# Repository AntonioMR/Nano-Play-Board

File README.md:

# Nano-Play-Board
Esta placa pretende ser una herramienta de iniciación a la experimentación y aprendizaje de recursos de programación y electrónica con la placa [Arduino Nano 3.x][3] o compatibles.
Dispone de varios sensores, actuadores y puertos para la conexión con otras placas de forma que sea posible explotar parte de las funcionalidades de la plataforma Arduino.

[José Juan Sánchez][1] ha desarrollado una librería para usar la placa que que se encuentra disponile en su [cuenta de github][2]. Esta librería permite un uso fácil de los recursos disponibles en la placa mediante el uso de las clases definidas para los distionts elementos y los metodos para la interactuación con los mismos. 

## Sensores
- Una fotoresistencia conectada al pin de entrada analógica A6.
- Un potenciómetro conectado al pin de entrada analógica A7.
- Cuatro pulsadores conectados a los pines PB0-3 del expansor de GPIO.
- Un acelerómetro de tres ejes conectado a los pines A4 y A5 por medio del bus I2C.
- Un encoder incremental de 16 pasos/revolución conectado a los pines D2 y D5.

## Actuadores
- Un buzzer conectado al canal 7 del driver para LED's.
- Un led RGB conectado a los canales 4, 5 y 6 (rojo, azul y verde respectivamente).
- Una matriz de led's conectada a los pines PA0-7 y PB4-7 del expansor de GPIO, para indicar la columna a encender como el patrón a visualizar en la columna. 

## Puertos
- Un zócalo hembra para conectar un detector de objetos por ultrasonidos conectado a los pines D7 y D8.
- Dos zócalos para conectar foto-receptores de infrarrojos tipo CNY-70 conectados a los pines D6 y D9.
- Un zócalo hembra para conectar un sensor de temperatura y humedad tipo DTH11/DTH22 conectado al pin D12.
- Cuatro zócalos macho para conectar servomotores controlados mediante los canales 0-4 del driver para LED's conectado por I2C.
- Un zócalo hembra para conectar un modulo Bluetooth HC-05/HC-6 mediante los pines D10 y D11.
- Un zócalo hembra para conectar un modulo Wifi ESP8266 mediante los pines D10 y D11.
- Cuatro pads para la conexion de sensores capacitivos a los pines A0, A1, A2 y A3.

## Estructura del repositorio
- Raiz: Fuentes del proyecto de la placa de circuito impreso para el software de diseño de PCB [KiCad][4].
- Gerber : Ficheros de fabricacion en formato Gerber de la placa de circuito impreso.
- Imagenes : Renders de la placa de circuito impreso.
- Pdf : Ficheros para el montaje en formato pdf. Esquema del circuito, situacion de componentes, etc.
- Modelos3D : Modelos 3D en formato .wrl para la visualizacion en el proyecto del diseño de la PCB.
- Soft/lib : Librerías para el uso de los distintos elementos presentes en la placa.
- Soft/src : Ejemplos de uso de la placa. 

## Imagenes
Cara superior

Cara inferior

## Lista de materiales
Refencias | Valor | Total Uds
----------|-------|-----------
| R1, R2, R20, R21, R22, R3, R4, R5, R6, R7 | [Resistencia 120 Ohm 1/8W](http://www.tme.eu/es/details/crcw0805120rfktabc/resistencias-smd-0805/vishay/) | 10
| R8, R9, R10, R11, R12, R13, R38, R40, R42, R49, R52,  | [Resistencia 1 KOhm 1/8W](http://www.tme.eu/es/details/crcw08051k00fkea/resistencias-smd-0805/vishay/) | 11
| R14 | [Resistencia 2 KOhm 1/8W](http://www.tme.eu/es/details/crcw08052k00fktabc/resistencias-smd-0805/vishay/) | 1
| R23, R32, R33, R34, R35  | [Resistencia 4.7 KOhm 1/8W](http://www.tme.eu/es/details/crcw08054k70fkea/resistencias-smd-0805/vishay/) | 5
| R15, R16, R17, R18, R19, R24, R25, R26, R27, R36, R39, R41, R47, R50 | [Resistencia 10 KOhm 1/8W](http://www.tme.eu/es/details/crcw080510k0fkea/resistencias-smd-0805/vishay/) | 14
| R43, R45  | [Resistencia 220 Ohm 1/8W](http://www.tme.eu/es/details/rc0805fr-07220r/resistencias-smd-0805/yageo/rc0805fr-07220rl/) | 2
| R44, R46, R48, R51  | [Resistencia 47 KOhm 1/8W](http://www.tme.eu/es/details/rc0805fr-0747k/resistencias-smd-0805/yageo/rc0805fr-0747kl/) | 4
| R28, R29, R30, R31 | [Resistencia 10 MOhm 1/8W](http://www.tme.eu/es/details/crcw080510k0fkea/resistencias-smd-0805/vishay/) | 4
| R37 | [Resistencia LDR](http://www.tme.eu/es/details/gm7516/fotoresistencias/wodeyijia/) | 1
| RV1 | [Potenciometro 10K](https://es.rs-online.com/web/p/potenciometros/7293622/)| 1
| C1, C2 | [Condensador electrolitico 0,33 uF 50V](http://www.tme.eu/es/details/uvz1h330mdd/condensadores-electroliticos-tht-105c/nichicon/) | 2
| C18, C20 | [Condensador cerámico 10 nF 25V](http://www.tme.eu/es/details/cl21b103kcannnc/condensadores-mlcc-smd-0805/samsung/) | 2
| C3, C7, C13, C14, C15, C16, C17, C19, C21 | [Condensador cerámico 100 nF 50V](http://www.tme.eu/es/details/cl21b104kbcnnnc/condensadores-mlcc-smd-0805/samsung/) | 7
| C5 | [Condensador ceramico 47 uF 16V](http://www.tme.eu/es/details/cl31a476mqhnnne/condensadores-mlcc-smd-1206/samsung/) | 1
| D1 | [Diodo 15MQ040N](http://www.tme.eu/es/details/15mq040n/diodos-schottky-smd/vishay/15mq040ntrpbf/) | 1
| CON1 | [Conector Barrel Jack 5.5/2.1](http://www.tme.eu/es/details/fc68148/conectores-dc/cliff/) | 1
| P1 | [Tira de pines hembra recto 2x4]() | 1 
| P2 | [Tira de pines hembra recto 1x6]() | 1 
| P4, P5, P6, P7 | [Tira de pines macho recto 1x3]() | 4
| P8 | [Tira de pines hembra recto 1x3]() | 1 
| P10, P9 | [Tira de pines hembra recto 1x4]() | 2 
| P11, P12 | [Tira de pines macho acodado 1x4]() | 2
| P5 | [Tira de pines hembra recto](http://www.tme.eu/es/details/zl262-40sg/regletas-y-enchufes-de-taco/ninigi/) | 3 pines
| P6 | [Tira de pines hembra recto](http://www.tme.eu/es/details/zl262-40sg/regletas-y-enchufes-de-taco/ninigi/) | 4 pines
| U1 | [Arduino Nano](https://www.arduino.cc/en/Main/ArduinoBoardNano) | 1
| U2 | [Regulador de tension 5VDC](http://www.tme.eu/es/details/lm7805ct/estabilizadores-de-tension-no-regulados/fairchild-semiconductor/) | 1
| U3 | [Expansor GPIO, MCP23017](http://www.tme.eu/es/details/mcp23017-e_so/multiplexores-y-conmutadores-analogicos/microchip-technology/) | 1
| U5 | [Matriz de Led's 7x5 Anodo](http://www.tme.eu/es/details/lmd07057bue-101a/pantallas-led-matrices/wenrun/) | 1
| U6 | [Driver para LED 8 canales, PCA9551](http://es.rs-online.com/web/p/drivers-de-display-led/0510730/) | 1
| U8 | [Acelerometro 3 ejes](https://es.rs-online.com/web/p/circuitos-integrados-de-acelerometro/8016873/?sra=pstk) | 1
| U9 | [Inversor CMOS Schmitt Trigger CD40106BM](http://www.tme.eu/es/details/cd40106bm/barreras-inversores/texas-instruments/) | 1
| Q1, Q2, Q3, Q4, Q5, Q8, Q9 | [Transistor NPN SMBT3904](http://www.tme.eu/es/details/smbt3904e6327/transistores-npn-smd/infineon-technologies/)| 7
| Q6, Q7 | [Transistor Mosfet canal N BSS138P](http://www.tme.eu/es/details/bss138p.215/transistores-con-canal-n-smd/nxp/)| 2
| LED1 | [Led RGB 5mm](http://www.tme.eu/es/details/ostama5b31a/diodos-led-tht-5mm/optosupply/)| 1
| SP1 | [Transductor de sonido piezoeléctrico](http://www.tme.eu/es/details/ld-bzpn-1705/transductores-piezoelect-sin-generador/loudity/)| 1
| SW1, SW2, SW3, SW4 | [Pulsador normalmente abierto](http://www.tme.eu/es/details/dtsm31nb/micro-conmutadores-tact-pcb/canal-electronic/dtsm-31n-b/)| 4
| B1 | [Codificador giratorio 2 canales](http://es.rs-online.com/web/p/codificadores-giratorios-mecanicos/6234215/)| 1

## Pines
Referencia | Pin 
----------|-------
| USB Tx | D0 |
| USB Rx | D1 |
| Encoder canal A | D2 |
| Interrupción Acelerómetro / Expansor GPIO | D3 |
| Reset perifericos | D4 |
| Encoder canal B | D5 |
| Infrarrojos Izquierdo | D6 |
| Ultrasonidos Echo | D7 |
| Ultrasonidos Trigg | D8 |
| Infrarrojos Derecho | D9 |
| Inalámbrico Tx | D10 |
| Inalámbrico Rx |  D11 |
| Sensor DTH Dato | D12 |
| Libre (LED Arduino) | D13 |
| Pad para sensor capacitivo 0 | A0 |
| Pad para sensor capacitivo 1 | A1 |
| Pad para sensor capacitivo 2 | A2 |
| Pad para sensor capacitivo 3 | A3 |
| I2C - SDA | A4 |
| I2C - SCL | A5 |
| LDR | A6 |
| Potenciometro | A7 |

## Licencia
Este diseño es Software Libre; usted puede redistribuirlo y/o modificarlo bajo los términos de la "GNU General Public License" como lo publica la "FSF Free Software Foundation", o (a su elección) de cualquier versión posterior.

Este diseño es distribuido con la esperanza de que le sea útil, pero SIN NINGUNA GARANTIA; incluso sin la garantía implícita por la VENTA o EJERCICIO DE ALGUN PROPOSITO en particular. Vea la "GNU General Public License" para más detalles.

## Creditos
Los modelos 3D de los siguientes componentes están creados a partir de los modelos originales indicados a continuación:

Componente | Autor | Modelo 
-----------|-------|--------
| Arduino Nano V3 | [Carlos AG][5] | [Modelo][6] 
| Bluetooth HC-06 | [Felix Georgievich ILgach][7] | [Modelo][8] 
| Detector HC-SR04 | [Renato Alonso Hurtado Medina][9] | [Modelo][10] 

[1]: http://josejuansanchez.org
[2]: https://github.com/josejuansanchez/NanoPlayBoard/
[3]: https://www.arduino.cc/en/Main/ArduinoBoardNano
[4]: http://kicad.org/
[5]: http://www.3dcontentcentral.com/Contributors.aspx?id=669699
[6]: http://www.3dcontentcentral.com/parts/download-part.aspx?id=387975&catalogid=171
[7]: http://www.3dcontentcentral.com/Contributors.aspx?id=1658685
[8]: http://www.3dcontentcentral.com/download-model.aspx?catalogid=171&id=542660
[9]: http://www.3dcontentcentral.com/Contributors.aspx?id=1704559
[10]: http://www.3dcontentcentral.com/download-model.aspx?catalogid=171&id=655885

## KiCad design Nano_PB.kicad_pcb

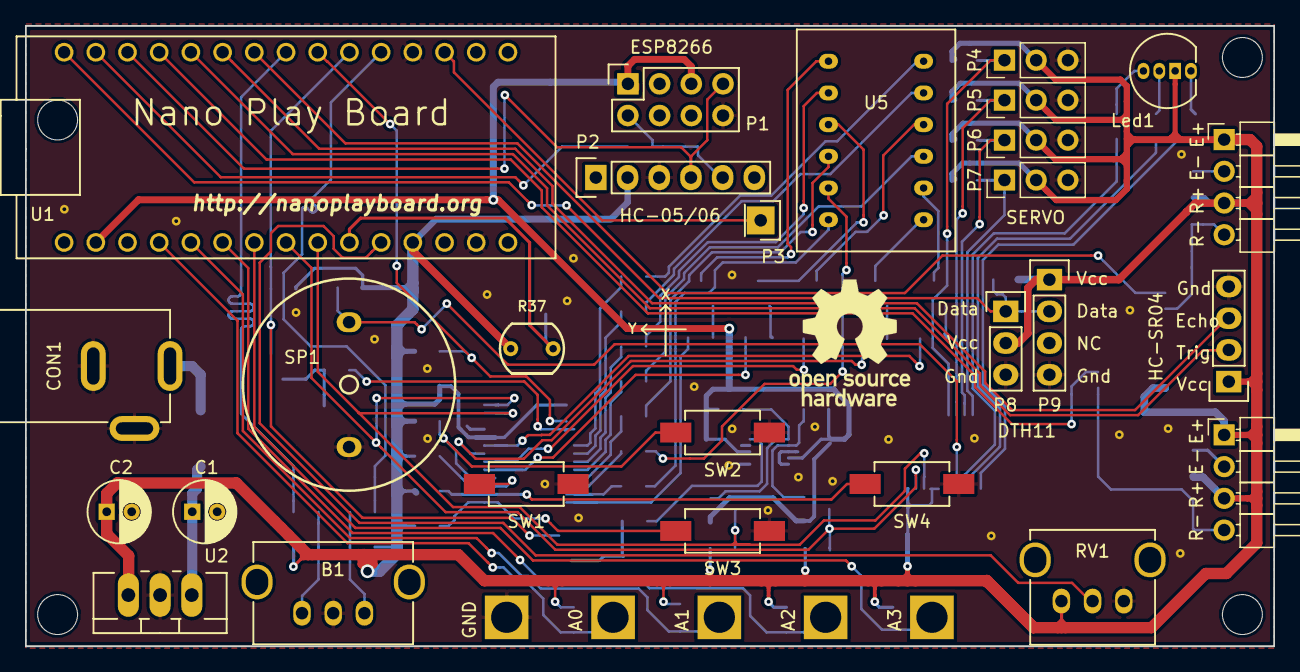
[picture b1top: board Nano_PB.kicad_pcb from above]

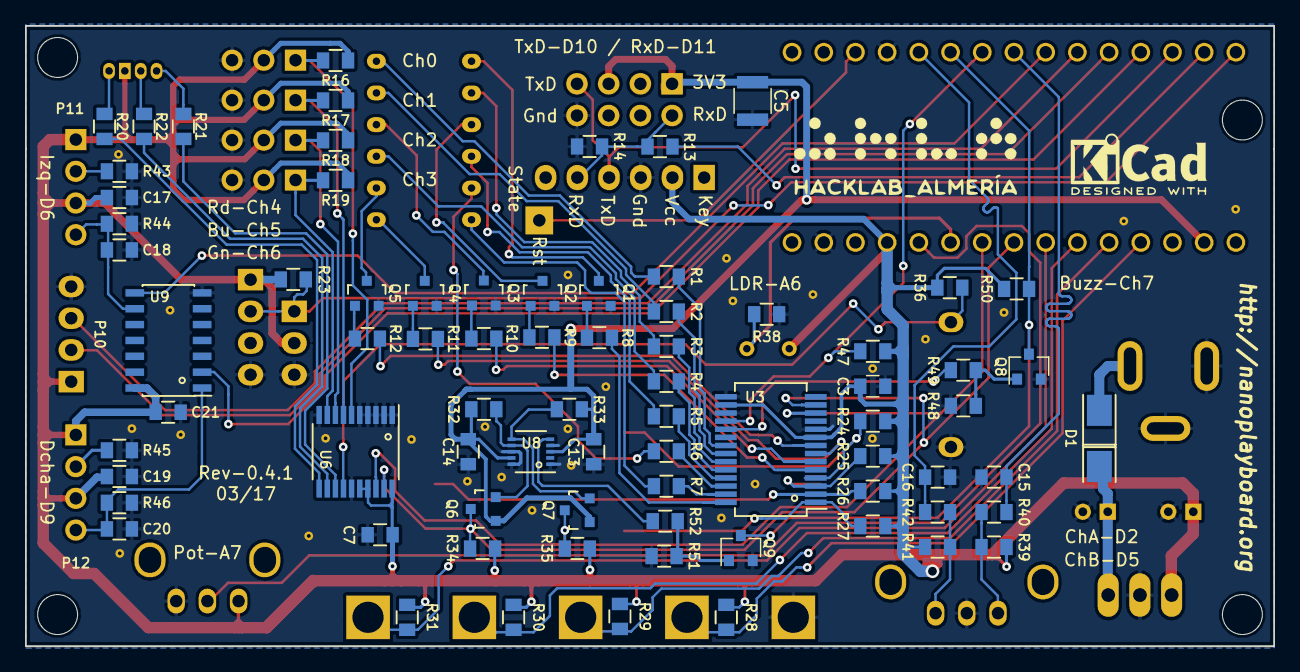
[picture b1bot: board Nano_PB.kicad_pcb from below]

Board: 2 copper layers, 100.0 x 49.7 mm, 135 parts (82 on the bottom side), 82 nets.

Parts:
B1: Encoder_Inc; ALPS_EC12E24_encoder_incremental
C1, C2: 0,33u; C_Radial_D5_L11_P2
C3, C7, C13, C14, C15, C16, C17, C19, C21: 100n; C_0805
C5: 47u; C_1210
C18, C20: 10n; C_0805
CON1: BARREL_JACK; Barrel_Jack_Hembra_CLIFF_FC68148
D1: 15MQ040N; DO-214AC
Gnd-Via: VAL**; Gnd-Via
Gnd-Via#2, Gnd-Via#3, Gnd-Via#4, Gnd-Via#5, Gnd-Via#6, Gnd-Via#7, Gnd-Via#8, Gnd-Via#9, Gnd-Via#10, Gnd-Via#11, Gnd-Via#12, Gnd-Via#13, Gnd-Via#14, Gnd-Via#15, Gnd-Via#16, Gnd-Via#17, Gnd-Via#18, Gnd-Via#19, Gnd-Via#20, Gnd-Via#21, Gnd-Via#22, Gnd-Via#23, Gnd-Via#24, Gnd-Via#25, Gnd-Via#26, Gnd-Via#27: VAL**; Gnd-Via
Led1: Led_RGB; LED_RGB_5mm_G_B_COM_R_Anodo_comun
P1: CONN_02X04; Socket_Strip_Straight_2x04
P2: CONN_01X06; Socket_Strip_Straight_1x06
P3: CONN_01X01; Socket_Strip_Straight_1x01
P4, P5, P6, P7: CONN_01X03; Pin_Header_Straight_1x03_Pitch2.54mm
P8: CONN_01X03; Socket_Strip_Straight_1x03
P9, P10: CONN_01X04; Socket_Strip_Straight_1x04
P11, P12: CONN_01X04; Pin_Header_Angled_1x04_Pitch2.54mm
P13, P14, P15, P16, P17: CONN_01X01; Pad_Conector_Cocodrilo
Q1, Q2, Q3, Q4, Q5, Q8, Q9: SMBT3904; SOT-23
Q6, Q7: BSS138; SOT-23
R1, R2, R3, R4, R5, R6, R7, R20, R21, R22: 120; R_0805
R8, R9, R10, R11, R12, R13, R38, R40, R42, R49, R52: 1K; R_0805
R14: 2K; R_0805
R16, R17, R18, R19, R24, R25, R26, R27, R36, R39, R41, R47, R50: 10K; R_0805
R23, R32, R33, R34, R35: 4K7; R_0805
R28, R29, R30, R31: 10M; R_0805
R37: LDR; LDR_TOKEN_PGM5_Series
R43, R45: 220R; R_0805
R44, R46, R48, R51: 47K; R_0805
RV1: 10K; ALP_RK09K111
SP1: BUZZER; LOUDITY_LD-BZPN-1705
SW1: Izquierda; CANAL_ELECTRONIC_DTSM-31N-B
SW2: Arriba; CANAL_ELECTRONIC_DTSM-31N-B
SW3: Abajo; CANAL_ELECTRONIC_DTSM-31N-B
SW4: Derecha; CANAL_ELECTRONIC_DTSM-31N-B
U1: Arduino_Nano
U2: LM7805CT; TO-220_Neutral123_Vertical_LargePads
U3: MCP23017; SSOP-28_5.3x10.2mm_Pitch0.65mm
U5: Matriz_5x7; Matriz_Led_7X5
U6: PCA9634; TSSOP-20_4.4x6.5mm_Pitch0.65mm
U8: MMA7660FC; DFN-10-1EP_3x3mm_Pitch0.5mm
U9: 40106; SOIC-14_3.9x8.7mm_Pitch1.27mm

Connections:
+3V3: C5.1, C13.1, C14.1, P1.1, P1.5, Q6.1, Q7.1, R32.1, R33.1, U1.17, U8.3, U8.9
+5V: C2.1, C3.1, C7.1, C17.1, C19.1, C21.1, Led1.3, P2.2, P4.2, P5.2, P6.2, P7.2, P8.2, P9.1, P10.1, P11.1, P11.3, P12.1, P12.3, R16.1, R17.1, R18.1, R19.1, R23.1, R24.1, R25.1, R26.1, R27.1, R28.1, R29.1, R30.1, R31.1, R34.1, R35.1, R36.1, R37.1, R39.1, R41.1, R47.1, R50.1, RV1.1, U1.27, U2.3, U3.9, U3.16, U6.16, U6.17, U6.20, U9.14
/Bluetooth/RxD: P1.2, P2.5, R13.1, R14.1
A0: P13.1, R28.2, U1.19
A1: P14.1, R29.2, U1.20
A2: P15.1, R30.2, U1.21
A3: P16.1, R31.2, U1.22
A4: Q6.3, R34.2, U1.23, U3.13, U6.19
A5: Q7.3, R35.2, U1.24, U3.12, U6.18
A6: R37.2, R38.2, U1.25
A7: RV1.2, U1.26
BUZZER: R36.2, SP1.1, U6.14
D2: C16.1, R42.2, U1.5
D3: Q8.3, Q9.3, R50.2, U1.6
D5: C15.1, R40.2, U1.8
D6: U1.9, U9.8
D7: P10.3, U1.10
D8: P10.2, U1.11
D9: U1.12, U9.2
D10: P1.7, P2.4, U1.13
D11: R13.2, U1.14
D12: P8.1, P9.2, R23.2, U1.15
GND: B1.C, C1.2, C2.2, C3.2, C5.2, C7.2, C13.2, C14.2, C15.2, C16.2, C17.2, C18.2, C19.2, C20.2, C21.2, CON1.2, CON1.3, Gnd-Via.1, Gnd-Via#2.1, Gnd-Via#3.1, Gnd-Via#4.1, Gnd-Via#5.1, Gnd-Via#6.1, Gnd-Via#7.1, Gnd-Via#8.1, Gnd-Via#9.1, Gnd-Via#10.1, Gnd-Via#11.1, Gnd-Via#12.1, Gnd-Via#13.1, Gnd-Via#14.1, Gnd-Via#15.1, Gnd-Via#16.1, Gnd-Via#17.1, Gnd-Via#18.1, Gnd-Via#19.1, Gnd-Via#20.1, Gnd-Via#21.1, Gnd-Via#22.1, Gnd-Via#23.1, Gnd-Via#24.1, Gnd-Via#25.1, Gnd-Via#26.1, Gnd-Via#27.1, P1.8, P2.3, P4.3, P5.3, P6.3, P7.3, P8.3, P9.4, P10.4, P17.1, Q1.2, Q2.2, Q3.2, Q4.2, Q5.2, Q8.2, Q9.2, R14.2, R38.1, R43.2, R44.2, R45.2, R46.2, R48.1, R51.1, RV1.3, SP1.2, SW1.1, SW2.1, SW3.1, SW4.1, U1.4, U1.29, U2.2, U3.10, U3.15, U3.17, U6.1, U6.2, U6.3, U6.4, U6.5, U6.10, U6.15, U8.1, U8.4, U8.8, U8.10, U9.7
LED_BLUE: R22.2, U6.12
LED_GREEN: R21.2, U6.13
LED_RED: R20.2, U6.11
unnamed: B1.A, R39.2, R40.1
unnamed: B1.B, R41.2, R42.1
unnamed: C1.1, D1.1, U2.1
unnamed: C18.1, P11.4, R44.1, U9.9
unnamed: C20.1, P12.4, R46.1, U9.1
unnamed: CON1.1, D1.2
unnamed: Led1.1, R21.1
unnamed: Led1.2, R22.1
unnamed: Led1.4, R20.1
unnamed: P11.2, R43.1
unnamed: P12.2, R45.1
unnamed: Q1.1, R8.1
unnamed: Q1.3, U5.1
unnamed: Q2.1, R9.1
unnamed: Q2.3, U5.3
unnamed: Q3.1, R10.1
unnamed: Q3.3, U5.10
unnamed: Q4.1, R11.1
unnamed: Q4.3, U5.7
unnamed: Q5.1, R12.1
unnamed: Q5.3, U5.8
unnamed: Q6.2, R32.2, U8.7
unnamed: Q7.2, R33.2, U8.6
unnamed: Q8.1, R48.2, R49.2
unnamed: Q9.1, R51.2, R52.2
unnamed: R1.1, U5.12
unnamed: R2.1, U5.11
unnamed: R3.1, U5.2
unnamed: R4.1, U5.9
unnamed: R5.1, U5.4
unnamed: R6.1, U5.5
unnamed: R7.1, U5.6
unnamed: R49.1, U3.19
unnamed: R52.1, U8.5
PA0: R1.2, U3.21
PA1: R2.2, U3.22
PA2: R3.2, U3.23
PA3: R4.2, U3.24
PA4: R5.2, U3.25
PA5: R6.2, U3.26
PA6: R7.2, U3.27
PA7: R8.2, U3.28
PB0: R27.2, SW3.2, U3.1
PB1: R26.2, SW4.2, U3.2
PB2: R25.2, SW1.2, U3.3
PB3: R24.2, SW2.2, U3.4
PB4: R9.2, U3.5
PB5: R10.2, U3.6
PB6: R11.2, U3.7
PB7: R12.2, U3.8
RESET: P3.1, U1.3
SERVO1: P4.1, R16.2, U6.6
SERVO2: P5.1, R17.2, U6.7
SERVO3: P6.1, R18.2, U6.8
SERVO4: P7.1, R19.2, U6.9
~RESET: R47.2, U1.7, U3.18

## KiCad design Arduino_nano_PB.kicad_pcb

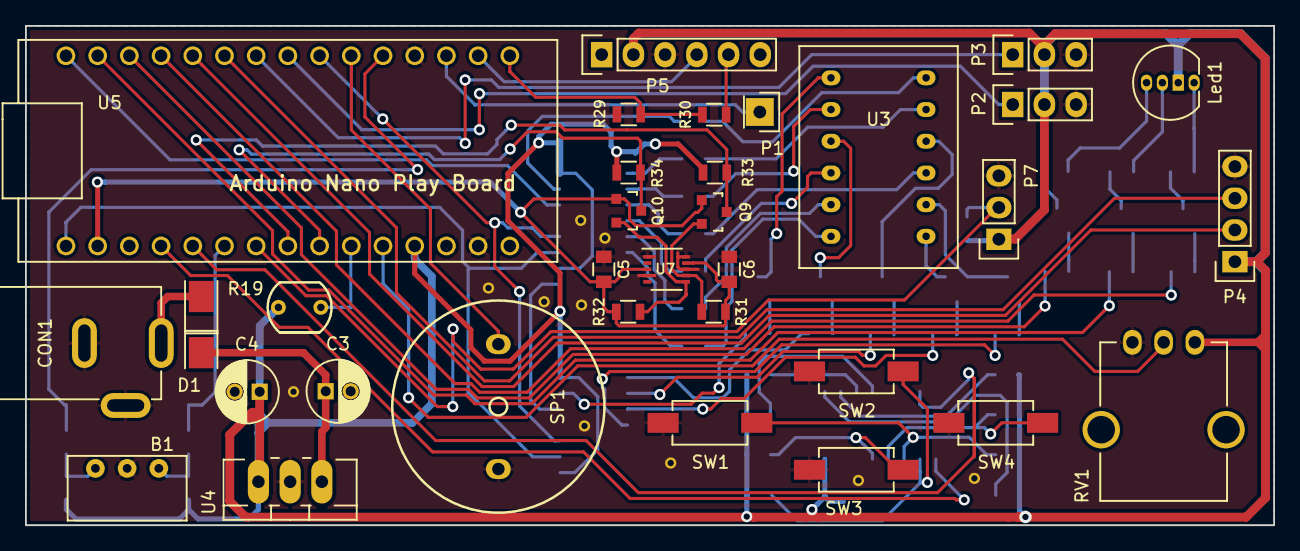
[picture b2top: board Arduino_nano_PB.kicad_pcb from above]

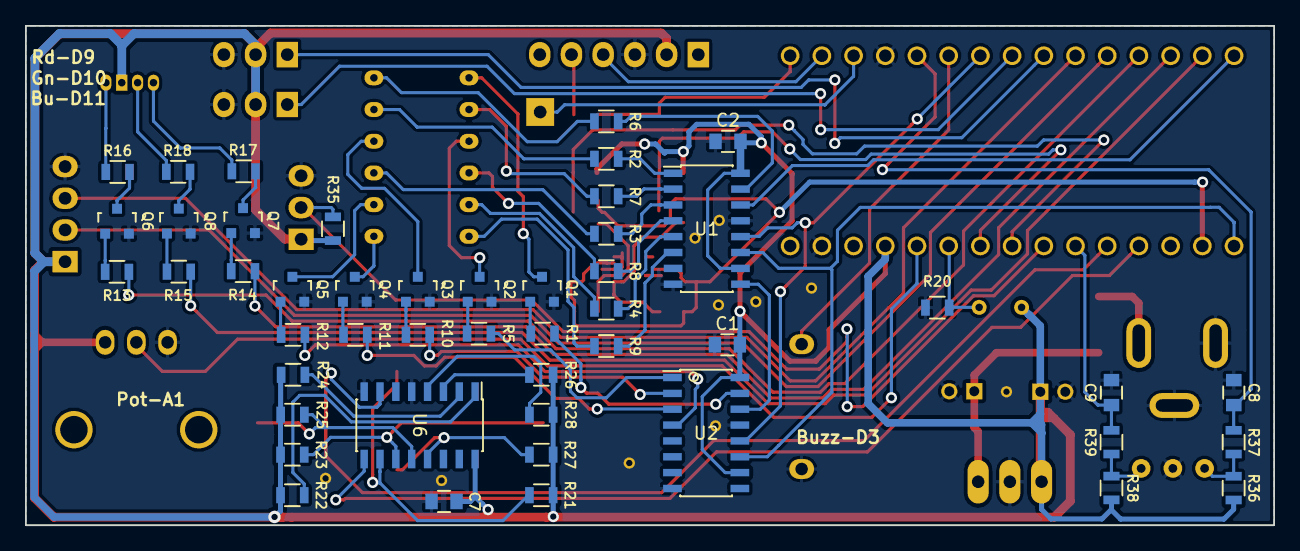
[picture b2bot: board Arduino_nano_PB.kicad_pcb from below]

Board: 2 copper layers, 100.0 x 40.0 mm, 91 parts (48 on the bottom side), 80 nets.

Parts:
B1: Encoder_Inc; Bourns_3315C_encoder_incremental
C1, C2, C5, C6, C7: 100n; C_0805
C3: 0,33u; C_Radial_D5_L11_P2
C4: 0,1u; C_Radial_D5_L11_P2
C8, C9: C; C_0805
CON1: BARREL_JACK; Barrel_Jack_Hembra_CLIFF_FC68148
D1: 1N4002; DO-214AC
Gnd-Via: VAL**; Gnd-Via
Gnd-Via#2, Gnd-Via#3, Gnd-Via#4, Gnd-Via#5, Gnd-Via#6, Gnd-Via#7, Gnd-Via#8, Gnd-Via#9, Gnd-Via#10: VAL**; Gnd-Via
Led1: Led_RGB; LED_RGB_5mm_G_B_COM_R_Anodo_comun
P1: CONN_01X01; Socket_Strip_Straight_1x01
P2, P3: CONN_01X03; Pin_Header_Straight_1x03
P4: CONN_01X04; Socket_Strip_Straight_1x04
P5: CONN_01X06; Socket_Strip_Straight_1x06
P7: CONN_01X03; Socket_Strip_Straight_1x03
Q1, Q2, Q3, Q4, Q5: SMBT3904; SOT-23
Q6, Q7, Q8: BC846B; SOT-23
Q9, Q10: BSS138; SOT-23
R1, R5, R10, R11, R12, R20, R30: 1K; R_0805
R2, R3, R4, R6, R7, R8, R9: 120; R_0805
R13, R14, R15, R31, R32, R33, R34: 4K7; R_0805
R16, R17, R18: 100; R_0805
R19: LDR; LDR_TOKEN_PGM5_Series
R21, R22, R23, R24, R25, R26, R27, R28: 10K; R_0805
R29: 2K; R_0805
R35, R36, R37, R38, R39: R; R_0805
RV1: 10K; POT_SR_PASIVES_R9011
SP1: BUZZER; LOUDITY_LD-BZPN-1705
SW1: Izquierda; CANAL_ELECTRONIC_DTSM-31N-B
SW2: Arriba; CANAL_ELECTRONIC_DTSM-31N-B
SW3: Abajo; CANAL_ELECTRONIC_DTSM-31N-B
SW4: Derecha; CANAL_ELECTRONIC_DTSM-31N-B
U1, U2: 74HC595; SOIC-16_3.9x9.9mm_Pitch1.27mm
U3: Matriz_5x7; Matriz_Led_7X5
U4: LM7805CT; TO-220_Neutral123_Vertical_LargePads
U5: Arduino_Nano
U6: 74HC148; SOIC-16_3.9x9.9mm_Pitch1.27mm
U7: MMA7660FC; DFN-10-1EP_3x3mm_Pitch0.5mm

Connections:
+3V3: C5.1, C6.1, Q9.1, Q10.1, R31.1, R32.1, U5.17, U7.3, U7.9
+5V: C1.1, C2.1, C4.1, C7.1, Led1.3, P2.2, P3.2, P4.1, P5.2, P7.1, R19.1, R21.1, R22.2, R23.1, R24.2, R25.1, R26.2, R27.1, R28.2, R33.1, R34.1, R35.1, R36.1, R38.1, RV1.1, U1.10, U1.16, U2.10, U2.16, U4.3, U5.27, U6.16
A0: U5.19, U6.9
A1: U5.20, U6.7
A2: C9.1, R39.2, U5.21
A3: P7.2, R35.2, U5.22
A4: Q9.3, R33.2, U5.23
A5: Q10.3, R34.2, U5.24
A6: R19.2, R20.2, U5.25
A7: RV1.2, U5.26
D0: P5.4, U5.2
D1: R29.1, R30.2, U5.1
D2: C8.1, R37.2, U5.5
D3: SP1.1, U5.6
D4: U1.12, U2.12, U5.7
D5: P2.1, U5.8
D6: P3.1, U5.9
D7: P4.3, U5.10
D8: P4.2, U5.11
D9: R13.2, U5.12
D10: R14.2, U5.13
D11: R15.2, U5.14
D12: U1.14, U5.15
D13: U1.11, U2.11, U5.16
GND: B1.C, C1.2, C2.2, C3.2, C4.2, C5.2, C6.2, C7.2, C8.2, C9.2, CON1.2, CON1.3, Gnd-Via.1, Gnd-Via#2.1, Gnd-Via#3.1, Gnd-Via#4.1, Gnd-Via#5.1, Gnd-Via#6.1, Gnd-Via#7.1, Gnd-Via#8.1, Gnd-Via#9.1, Gnd-Via#10.1, P2.3, P3.3, P4.4, P5.3, P7.3, Q1.2, Q2.2, Q3.2, Q4.2, Q5.2, Q6.2, Q7.2, Q8.2, R20.1, R29.2, RV1.3, SP1.2, SW1.1, SW2.1, SW3.1, SW4.1, U1.8, U1.13, U2.8, U2.13, U4.2, U5.4, U5.29, U6.5, U6.8, U7.1, U7.4, U7.8, U7.10
unnamed: B1.A, R36.2, R37.1
unnamed: B1.B, R38.2, R39.1
unnamed: C3.1, D1.1, U4.1
unnamed: CON1.1, D1.2
unnamed: Led1.1, R17.1
unnamed: Led1.2, R18.1
unnamed: Led1.4, R16.1
unnamed: P5.5, R30.1
unnamed: Q1.1, R1.1
unnamed: Q1.3, U3.1
unnamed: Q2.1, R5.1
unnamed: Q2.3, U3.3
unnamed: Q3.1, R10.1
unnamed: Q3.3, U3.10
unnamed: Q4.1, R11.1
unnamed: Q4.3, U3.7
unnamed: Q5.1, R12.1
unnamed: Q5.3, U3.8
unnamed: Q6.1, R13.1
unnamed: Q6.3, R16.2
unnamed: Q7.1, R14.1
unnamed: Q7.3, R17.2
unnamed: Q8.1, R15.1
unnamed: Q8.3, R18.2
unnamed: Q9.2, R31.2, U7.7
unnamed: Q10.2, R32.2, U7.6
unnamed: R1.2, U2.15
unnamed: R2.1, U3.11
unnamed: R2.2, U1.1
unnamed: R3.1, U3.9
unnamed: R3.2, U1.3
unnamed: R4.1, U3.5
unnamed: R4.2, U1.5
unnamed: R5.2, U2.1
unnamed: R6.1, U3.12
unnamed: R6.2, U1.15
unnamed: R7.1, U3.2
unnamed: R7.2, U1.2
unnamed: R8.1, U3.4
unnamed: R8.2, U1.4
unnamed: R9.1, U3.6
unnamed: R9.2, U1.6
unnamed: R10.2, U2.2
unnamed: R11.2, U2.3
unnamed: R12.2, U2.4
unnamed: R21.2, SW2.2, U6.10
unnamed: R22.1, U6.1
unnamed: R23.2, SW1.2, U6.11
unnamed: R24.1, U6.2
unnamed: R25.2, SW4.2, U6.12
unnamed: R26.1, U6.3
unnamed: R27.2, SW3.2, U6.13
unnamed: R28.1, U6.4
unnamed: U1.9, U2.14
RESET: P1.1, U5.3

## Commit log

2016-03-12 commit inicial
2016-03-12 añadir imagenes y comenzar BOM
2016-03-12 corregido problema en los gerber de la cara bottom
2016-03-13 actualizar lista de materiales
2016-03-13 error de formato en lista de materiales
2016-03-13 añadir valores en esquema y reordenar PCB
2016-03-13 Añadir serigrafia capa bottom
2016-03-13 Actualizar imagenes serigrafia
2016-03-13 Ajustar margen mascara soldadura a 7 mil
2016-03-14 incrementar corona de pads y vias a 0.2mm min
2016-03-26 corregir errata en readme y capa de serigrafia superior
2016-04-14 modificar tamaños de taladros en led RGB y resistencias
2016-05-23 Añadiendo Pines al Read.me
    Añadiendo Pines al Read.me
    Me pareció complicado encontrarlos y los pongo por si alguien lo necesita :)
2016-05-30 Añadido esquema electrico y distribucion de componentes
2016-06-01 modificado fichero pdf con esquema
2016-06-01 añadido ejemplo uso matriz
2016-06-05 Añadida libreria para representar caracteres. modificado ejemplo
2016-06-12 Modificado Readme.md
2016-06-12 Modificada libreria registro para usar el pin D6 vs A7.
2016-06-24 añadidas referencia a la libreria desarollada por @josejuansanchez y puertos disponibles
2016-06-24 añadir salto de linea
2016-07-18 corrige issue #2
2016-07-18 actualizar imagenes y descripción
2016-07-24 Añadidos nuevos elementos al esquema de la placa
2016-07-29 añaadido zocalo para sensor de temperatura y primera distribucion sobre la PCB
2016-07-31 finalizado enrutado provisional
2016-08-06 finalizado el trazado y renombrado de archivos
2016-08-06 Actualizados nuevos sensores en readme
2016-08-06 añadiendo valores del distribuidor a los componentes
2016-08-06 ordenar referencias de componentes
2016-08-07 ajustes en serigrafia y posicion de algunos componentes
2016-08-07 Pcb enviada a fabricar
2016-08-07 fichero borrado
2016-08-07 actualizar imagenes de la placa
2016-08-07 Actualizado el esquema electrico
2016-08-08 Añadir modelos 3D
2016-08-08 pequeña errata
2016-08-08 pequeña errata otra vez
2016-08-08 se resiste la tabla
2016-08-11 corregir formato en tabla
2016-09-16 corrige issue #10
2016-09-16 actualizar pdf de guia para la fabricacion
2016-10-11 cambiados encoder y potenciometro
2017-01-07 añadidos driver para led y conectores para fotodiodos infrarrojos
2017-01-11 Modificada posicion pulsadores y añadir vias entre planos de masa
2017-01-12 corregida serigrafia inferior
2017-01-13 modificada posicion del modulo esp
2017-01-13 modificaciones menores en el trazado para optimizarlo
2017-01-14 completar serigrafias
2017-01-14 modificada posicion transistores bus I2C
2017-01-14 ultimas modificaciones a la PCB
2017-01-14 actualizar lista de componentes y descripcion en README
2017-01-14 actualizada tabla de uso de pines Arduino
2017-01-15 modificar imagenes de la placa
2017-01-16 añadidos pdf para montaje
2017-01-19 Se añade un expansor GPIO al esquema y se elminan registros y codificador
2017-01-21 finalizada la ubicacion de componentes para la V0.4
2017-01-23 ordenar trazado, añadir vias de union de planos gnd
2017-01-24 Modificaciones menores en serigrafia
2017-01-25 Revisado V0.4. Actualizados gerber y esquemas
2017-01-25 version definitiva V0.4
2017-01-25 actualizado README y BOM a la V0.4
2017-03-03 corregir errata en valores BOM
2017-03-03 corregidos valores en esquema y simbolos corruptos
2017-03-03 cambiadas huellas erroneas en U3 y U9. Corrige issues #17 y #18
2017-03-04 modificar posicion de vias de alimentacion proximas al chasis del encoder
2017-03-07 finalizada V0.4.1 corrige #17, #18 y #19
